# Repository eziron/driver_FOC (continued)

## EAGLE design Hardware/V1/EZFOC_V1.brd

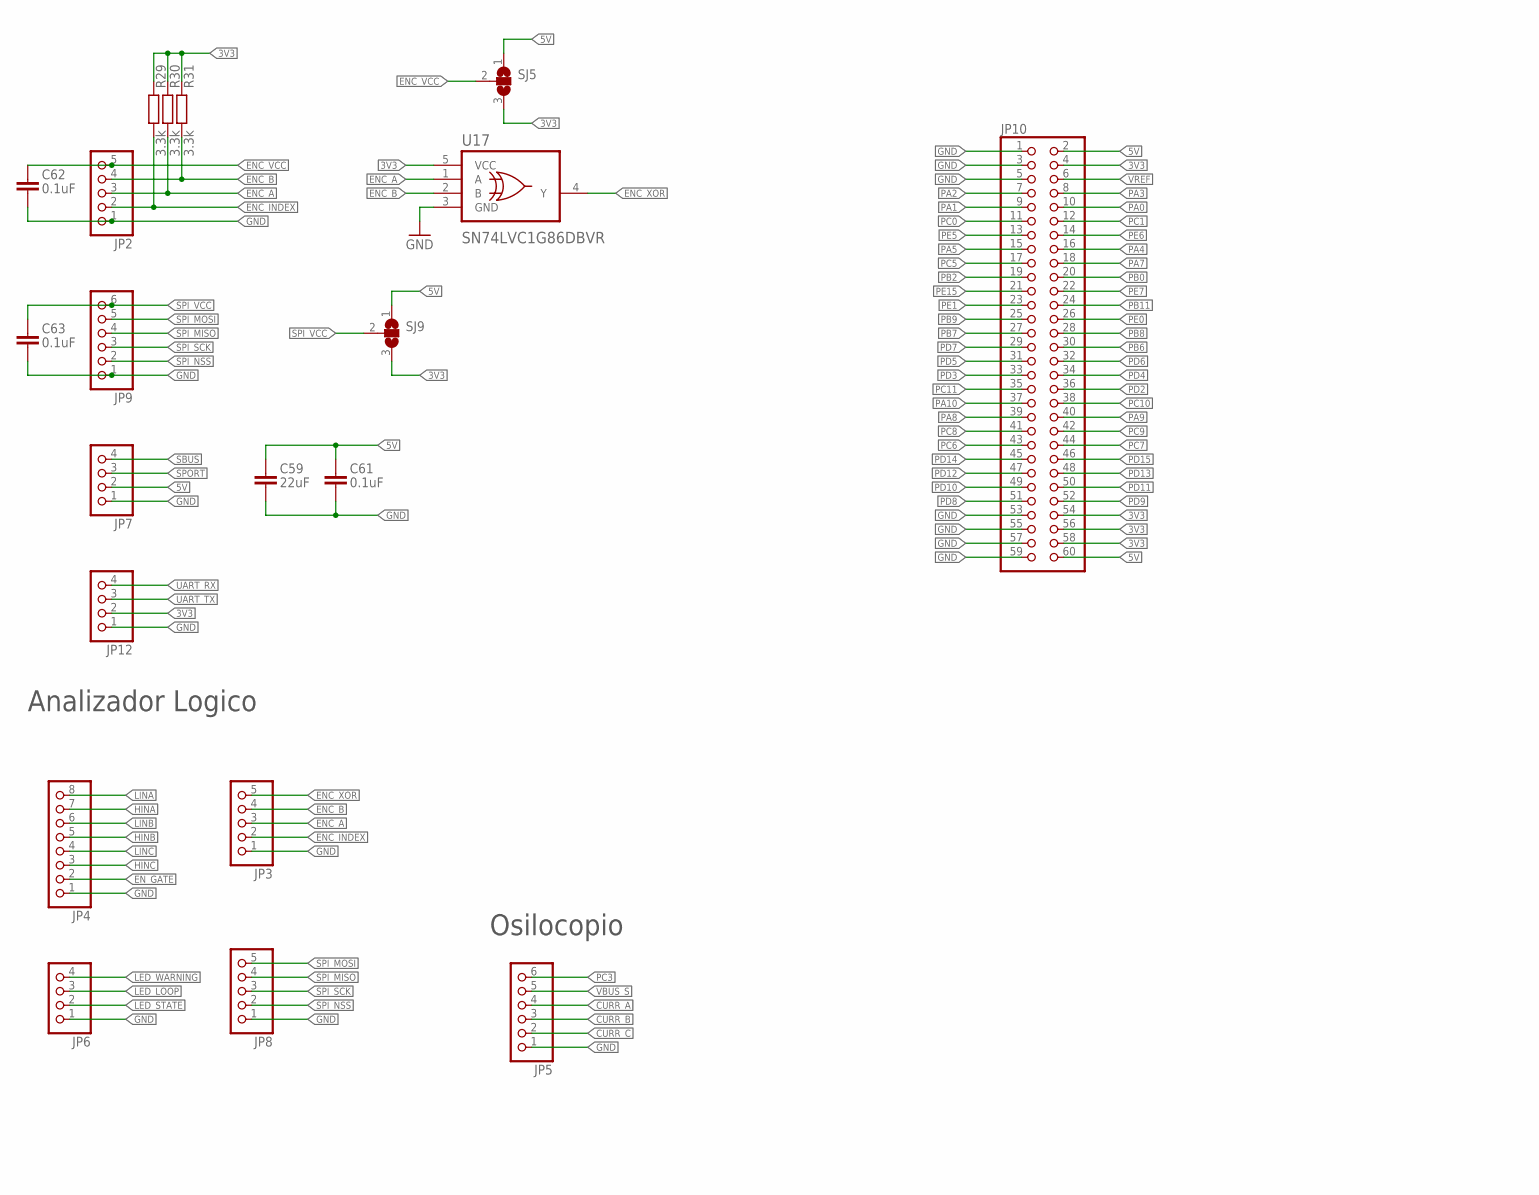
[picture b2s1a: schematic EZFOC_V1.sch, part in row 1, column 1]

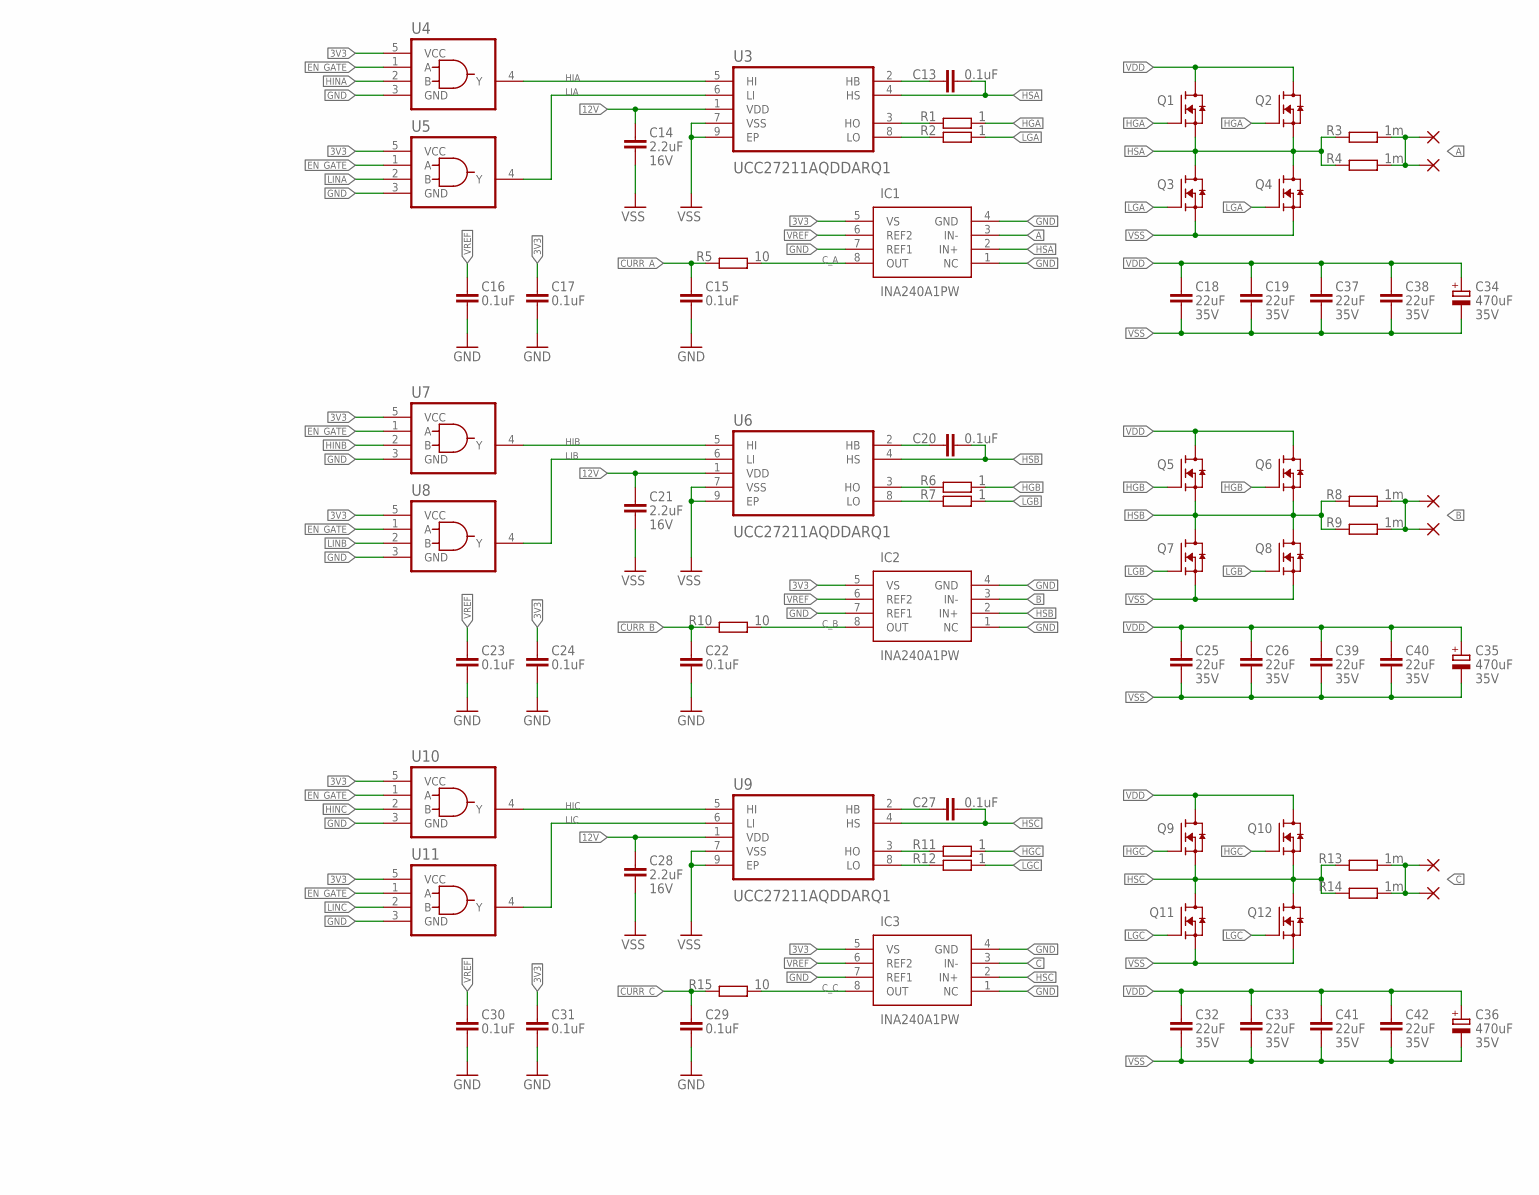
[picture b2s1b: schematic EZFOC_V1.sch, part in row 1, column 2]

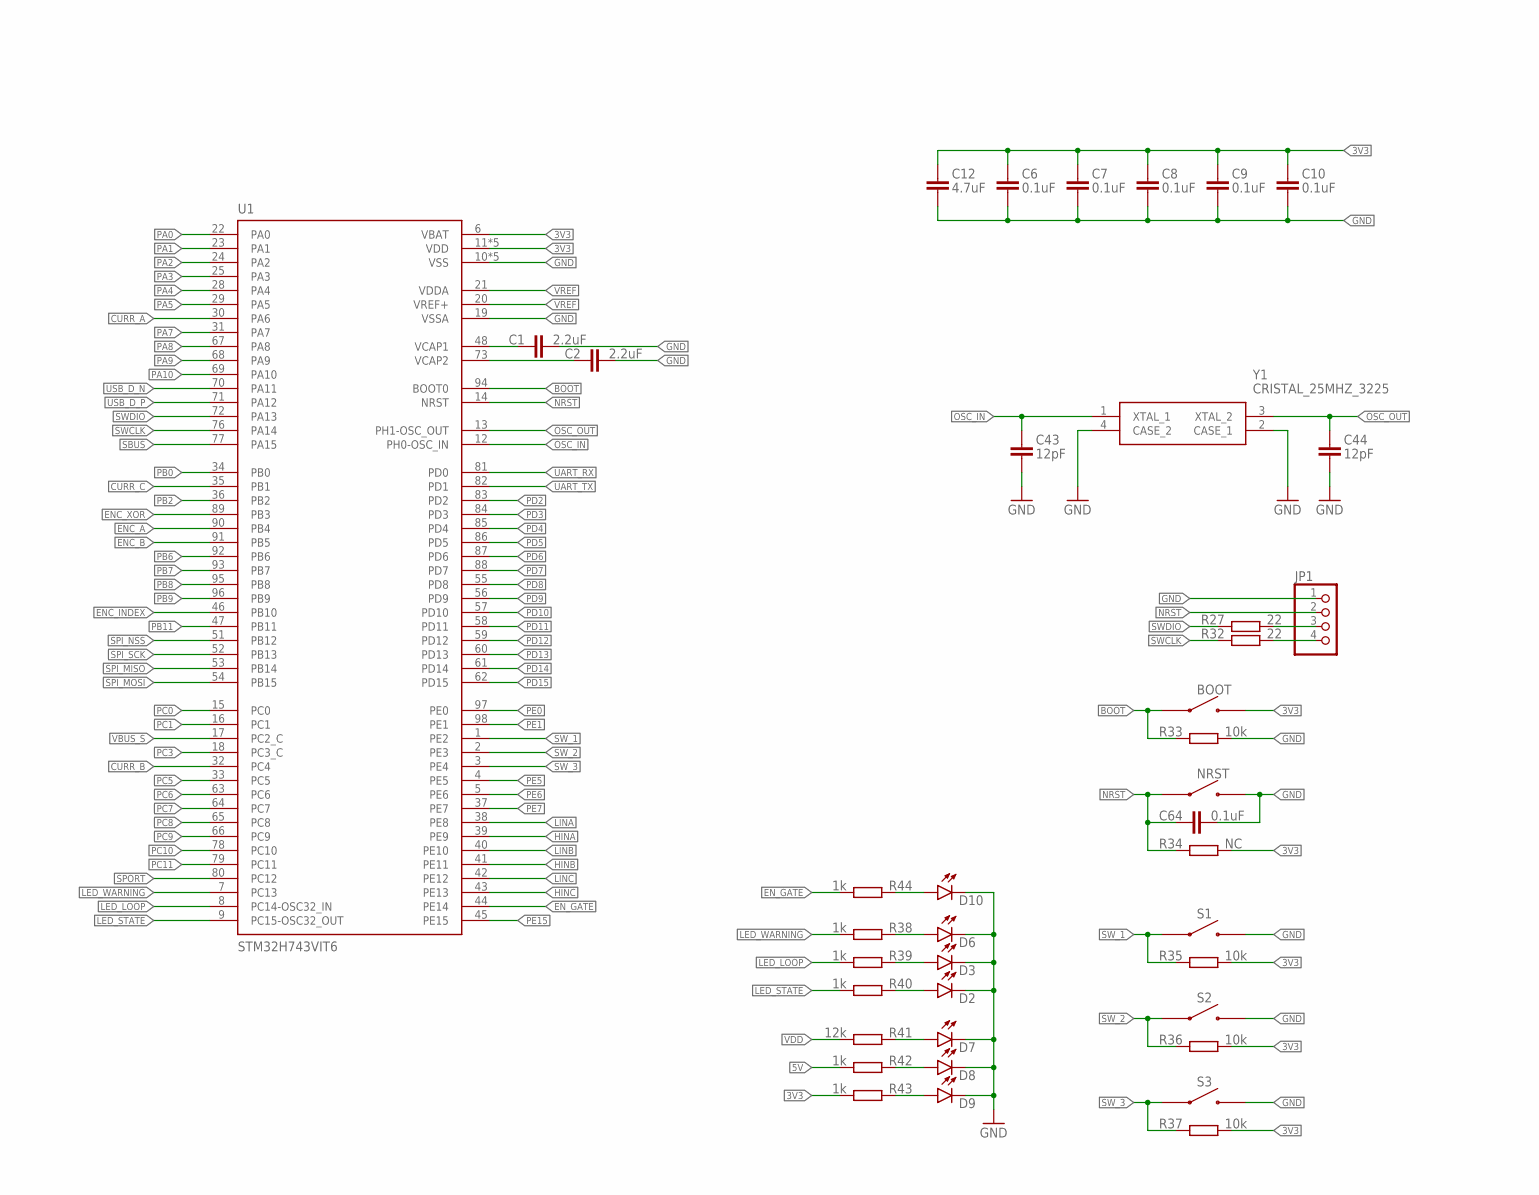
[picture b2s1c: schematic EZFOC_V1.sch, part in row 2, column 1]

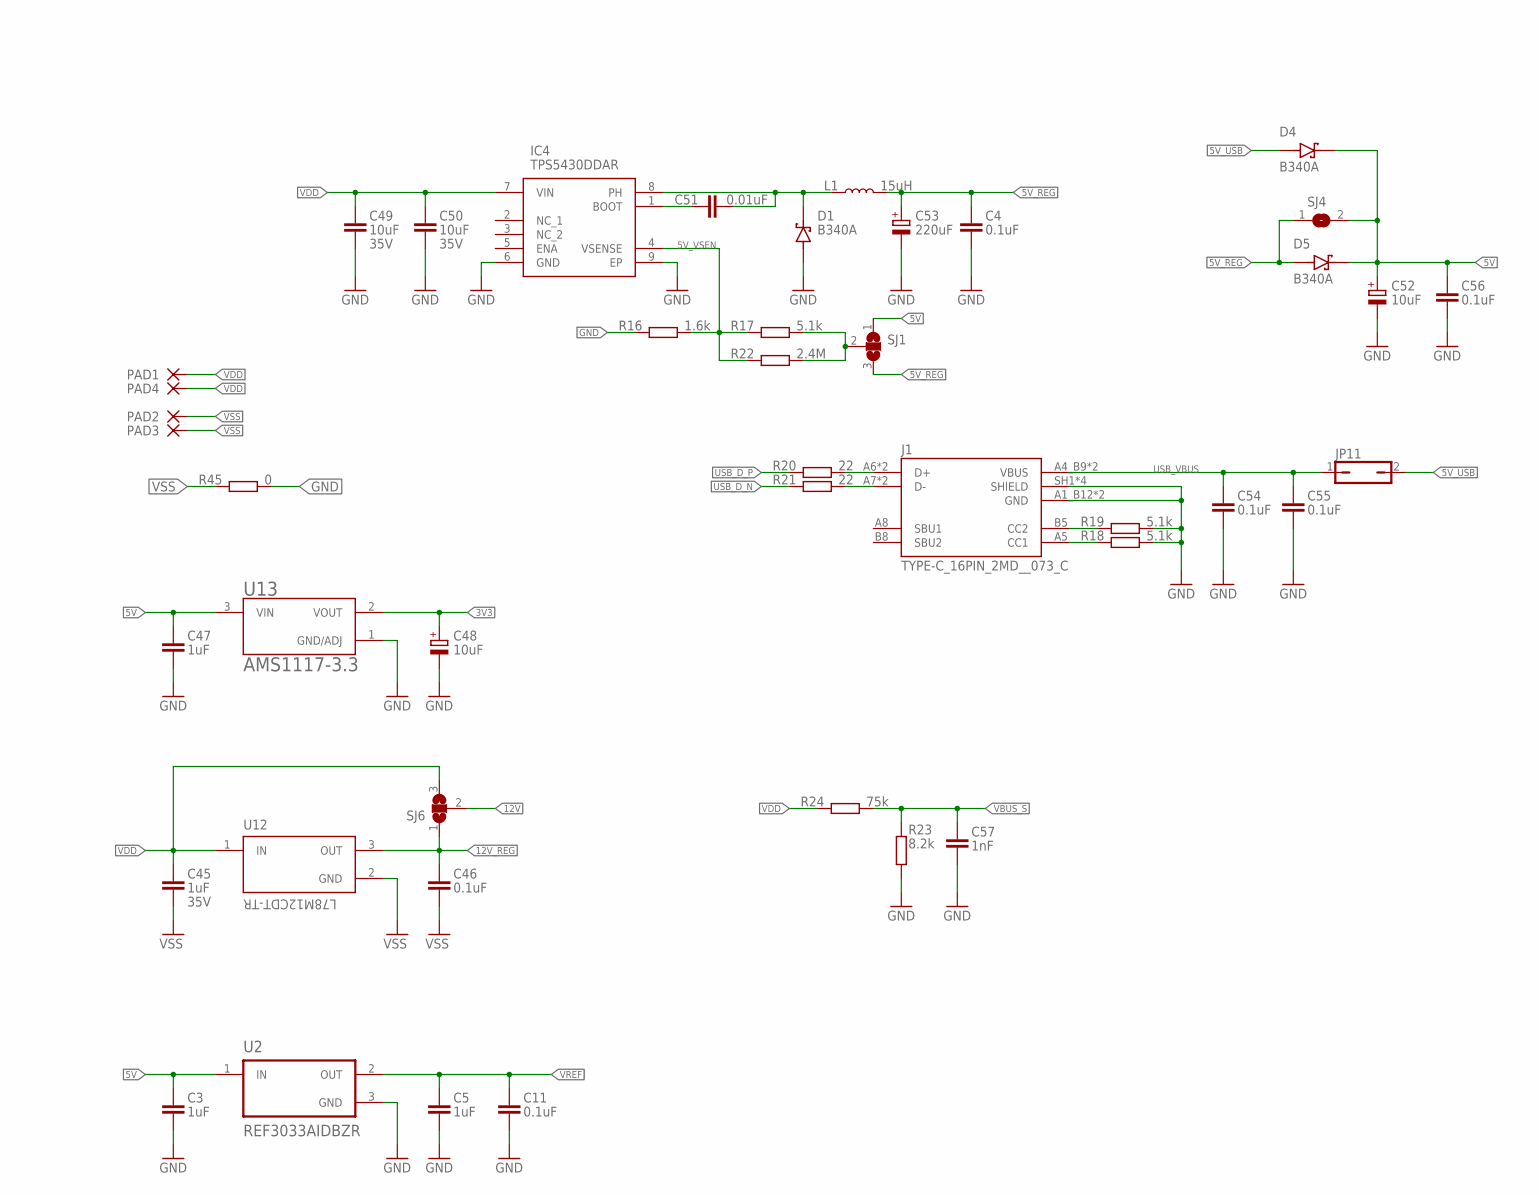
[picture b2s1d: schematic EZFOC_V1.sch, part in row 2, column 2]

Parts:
A, A1: PAD1.27X2.54; SMD1,27-2,54
B, B1: PAD1.27X2.54; SMD1,27-2,54
BOOT: TS-1088; SKRKAEE020
C, C65: PAD1.27X2.54; SMD1,27-2,54
C1, C2: 2.2uF; 0603
C3, C5, C45, C47: 1uF; 0603; VOLTAGE_RATING 35V
C4, C6, C7, C8, C9, C10, C11, C15, C16, C17, C22, C23, C24, C29, C30, C31, C46, C54, C55, C56, C61, C62, C63, C64: 0.1uF; 0402
C12: 4.7uF; 0603
C13, C20, C27: 0.1uF; 0603; VOLTAGE_RATING 35V
C14, C21, C28: 2.2uF; 0603; VOLTAGE_RATING 16V
C18, C19, C25, C26, C32, C33, C37, C38, C39, C40, C41, C42, C59: 22uF; 1206; VOLTAGE_RATING 35V
C34, C35, C36: 470uF; CAPAE1030X1050N; VOLTAGE_RATING 35V; JLCPCB C2980172
C43, C44: 12pF; 0402
C48, C52: 10uF; CAPMP3216X180N; JLCPCB C7171
C49, C50: 10uF; 0805; VOLTAGE_RATING 35V
C51: 0.01uF; 0603
C53: 220uF; CAPAE660X800N; JLCPCB C72494
C57: 1nF; 0402
D1, D4, D5: B340A; DIOM5226X240N; JLCPCB C8678
D2, D3: LED_BLUE; LEDC2012X110N_FLAT-B; JLCPCB C965817
D6: LED_BLUE; LEDC2012X110N_FLAT-B; JLCPCB C2296
D7, D8, D9: LED_BLUE; LEDC2012X110N_FLAT-B; JLCPCB C84256
D10: LED_BLUE; LEDC2012X110N_FLAT-B; JLCPCB C2297
IC1, IC2, IC3: INA240A1PW; SOP65P640X120-8N; JLCPCB C93965
IC4: TPS5430DDAR; SOIC127P600X170-9N
J1: TYPE-C_16PIN_2MD__073_C; GCT_USB4105-GF-A
JP1, JP6, JP7, JP12: PINHD-1X4; 1X04
JP2, JP3, JP8: PINHD-1X5; 1X05
JP4: PINHD-1X8; 1X08
JP5, JP9: PINHD-1X6; 1X06
JP10: PINHD-2X30; 2X30
JP11: JP1Q; JP1
L1: 15uH; SMD6.6X7.3MM
NRST: TS-1088; SKRKAEE020
PAD1, PAD2, PAD3, PAD4: PAD2.54X5.08; SMD2,54-5,08
Q1, Q2, Q3, Q4, Q5, Q6, Q7, Q8, Q9, Q10, Q11, Q12: BSC011N03LSI_FL; TDSON-8FL
R1, R2, R6, R7, R11, R12: 1; 0603
R3, R4, R8, R9, R13, R14: 1m; 2512; JLCPCB C7370895
R5, R10, R15: 10; 0402
R16: 1.6k; 0603
R17, R18, R19: 5.1k; 0603
R20, R21, R27, R32: 22; 0402
R22: 2.4M; 0603
R23: 8.2k; 0603
R24: 75k; 0603
R29, R30, R31: 3.3k; 0402
R33, R35, R36, R37: 10k; 0402
R34: NC; 0402
R38, R39, R40, R42, R43, R44: 1k; 0402
R41: 12k; 0402
R45: 0; 1206; JLCPCB C17888
S1, S2, S3: TS-1088; SKRKAEE020
SJ1, SJ5, SJ6, SJ9: SJ2W; SJ_2
SJ4: SJ
U1: STM32H743VIT6; LQFP100
U2: REF3033AIDBZR; SOT95P237X112-3N
U3, U6, U9: UCC27211AQDDARQ1; SOIC127P600X170-9N
U4, U5, U7, U8, U10, U11: SN74LVC1G08DBVR; SOT95P280X145-5N
U12: L78M12CDT-TR; VREG_L78M12CDT-TR
U13: AMS1117-3.3; SOT229P700X180-4N
U17: SN74LVC1G86DBVR; SOT95P280X145-5N
Y1: CRISTAL_25MHZ_3225; SMD3225-4P

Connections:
3V3: BOOT.2, C6.1, C7.1, C8.1, C9.1, C10.1, C12.1, C17.1, C24.1, C31.1, C48.1 (+), IC1.5 (VS), IC2.5 (VS), IC3.5 (VS), JP10.4, JP10.54, JP10.56, JP10.58, JP12.2, R29.1, R30.1, R31.1, R34.2, R35.2, R36.2, R37.2, R43.2, SJ5.3, SJ9.3, U1.6 (VBAT), U1.11 (VDD), U1.27 (VDD), U1.50 (VDD), U1.75 (VDD), U1.100 (VDD), U4.5 (VCC), U5.5 (VCC), U7.5 (VCC), U8.5 (VCC), U10.5 (VCC), U11.5 (VCC), U13.2 (VOUT), U17.5 (VCC)
5V: C3.1, C47.1, C52.1 (+), C56.1, C59.1, C61.1, D4.C, D5.C, JP7.2, JP10.2, JP10.60, R42.2, SJ1.1, SJ4.2, SJ5.1, SJ9.1, U2.1 (IN), U13.3 (VIN)
5V_REG: C4.1, C53.1 (+), D5.A, L1.2, SJ1.3, SJ4.1
5V_USB: D4.A, JP11.2
5V_VSEN: IC4.4 (VSENSE), R16.2, R17.1, R22.1
12V: C14.1, C21.1, C28.1, SJ6.2, U3.1 (VDD), U6.1 (VDD), U9.1 (VDD)
12V_REG: C46.1, SJ6.1, U12.3 (OUT)
A: A.1, A1.1, IC1.3 (IN-), R3.2, R4.2
B: B.1, B1.1, IC2.3 (IN-), R8.2, R9.2
BOOT: BOOT.1, R33.1, U1.94 (BOOT0)
C: C.1, C65.1, IC3.3 (IN-), R13.2, R14.2
CURR_A: C15.1, JP5.4, R5.1, U1.30 (PA6)
CURR_B: C22.1, JP5.3, R10.1, U1.32 (PC4)
CURR_C: C29.1, JP5.2, R15.1, U1.35 (PB1)
C_A: IC1.8 (OUT), R5.2
C_B: IC2.8 (OUT), R10.2
C_C: IC3.8 (OUT), R15.2
ENC_A: JP2.3, JP3.3, R30.2, U1.90 (PB4), U17.1 (A)
ENC_B: JP2.4, JP3.4, R31.2, U1.91 (PB5), U17.2 (B)
ENC_INDEX: JP2.2, JP3.2, R29.2, U1.46 (PB10)
ENC_VCC: C62.1, JP2.5, SJ5.2
ENC_XOR: JP3.5, U1.89 (PB3), U17.4 (Y)
EN_GATE: JP4.2, R44.2, U1.44 (PE14), U4.1 (A), U5.1 (A), U7.1 (A), U8.1 (A), U10.1 (A), U11.1 (A)
EN_GATE_R: D10.A, R44.1
GND: C1.2, C2.2, C3.2, C4.2, C5.2, C6.2, C7.2, C8.2, C9.2, C10.2, C11.2, C12.2, C15.2, C16.2, C17.2, C22.2, C23.2, C24.2, C29.2, C30.2, C31.2, C43.2, C44.2, C47.2, C48.2 (-), C49.2, C50.2, C52.2 (-), C53.2 (-), C54.2, C55.2, C56.2, C57.2, C59.2, C61.2, C62.2, C63.2, C64.2, D1.A, D2.C, D3.C, D6.C, D7.C, D8.C, D9.C, D10.C, IC1.1 (NC), IC1.4 (GND), IC1.7 (REF1), IC2.1 (NC), IC2.4 (GND), IC2.7 (REF1), IC3.1 (NC), IC3.4 (GND), IC3.7 (REF1), IC4.6 (GND), IC4.9 (EP), J1.A1_B12 (GND), J1.B1_A12 (GND), J1.SH1 (SHIELD), J1.SH2 (SHIELD), J1.SH3 (SHIELD), J1.SH4 (SHIELD), JP1.1, JP2.1, JP3.1, JP4.1, JP5.1, JP6.1, JP7.1, JP8.1, JP9.1, JP10.1, JP10.3, JP10.5, JP10.53, JP10.55, JP10.57, JP10.59, JP12.1, NRST.2, R16.1, R18.2, R19.2, R23.1, R33.2, R45.2, S1.2, S2.2, S3.2, U1.10 (VSS), U1.19 (VSSA), U1.26 (VSS), U1.49 (VSS), U1.74 (VSS), U1.99 (VSS), U2.3 (GND), U4.3 (GND), U5.3 (GND), U7.3 (GND), U8.3 (GND), U10.3 (GND), U11.3 (GND), U13.1 (GND/ADJ), U17.3 (GND), Y1.2 (CASE_1), Y1.4 (CASE_2)
HBA: C13.1, U3.2 (HB)
HBB: C20.1, U6.2 (HB)
HBC: C27.1, U9.2 (HB)
HGA: Q1.4 (G), Q2.4 (G), R1.2
HGB: Q5.4 (G), Q6.4 (G), R6.2
HGC: Q9.4 (G), Q10.4 (G), R11.2
HIA: U3.5 (HI), U4.4 (Y)
HIB: U6.5 (HI), U7.4 (Y)
HIC: U9.5 (HI), U10.4 (Y)
HINA: JP4.7, U1.39 (PE9), U4.2 (B)
HINB: JP4.5, U1.41 (PE11), U7.2 (B)
HINC: JP4.3, U1.43 (PE13), U10.2 (B)
HOA: R1.1, U3.3 (HO)
HOB: R6.1, U6.3 (HO)
HOC: R11.1, U9.3 (HO)
HSA: C13.2, IC1.2 (IN+), Q1.1 (S), Q1.2 (S), Q1.3 (S), Q1.10 (S), Q2.1 (S), Q2.2 (S), Q2.3 (S), Q2.10 (S), Q3.5 (D), Q3.6 (D), Q3.7 (D), Q3.8 (D), Q3.9 (D), Q4.5 (D), Q4.6 (D), Q4.7 (D), Q4.8 (D), Q4.9 (D), R3.1, R4.1, U3.4 (HS)
HSB: C20.2, IC2.2 (IN+), Q5.1 (S), Q5.2 (S), Q5.3 (S), Q5.10 (S), Q6.1 (S), Q6.2 (S), Q6.3 (S), Q6.10 (S), Q7.5 (D), Q7.6 (D), Q7.7 (D), Q7.8 (D), Q7.9 (D), Q8.5 (D), Q8.6 (D), Q8.7 (D), Q8.8 (D), Q8.9 (D), R8.1, R9.1, U6.4 (HS)
HSC: C27.2, IC3.2 (IN+), Q9.1 (S), Q9.2 (S), Q9.3 (S), Q9.10 (S), Q10.1 (S), Q10.2 (S), Q10.3 (S), Q10.10 (S), Q11.5 (D), Q11.6 (D), Q11.7 (D), Q11.8 (D), Q11.9 (D), Q12.5 (D), Q12.6 (D), Q12.7 (D), Q12.8 (D), Q12.9 (D), R13.1, R14.1, U9.4 (HS)
LED1R: D6.A, R38.1
LED2R: D3.A, R39.1
LED3R: D2.A, R40.1
LED4R: D7.A, R41.1
LED5R: D8.A, R42.1
LED6R: D9.A, R43.1
LED_LOOP: JP6.3, R39.2, U1.8 (PC14-OSC32_IN)
LED_STATE: JP6.2, R40.2, U1.9 (PC15-OSC32_OUT)
LED_WARNING: JP6.4, R38.2, U1.7 (PC13)
LGA: Q3.4 (G), Q4.4 (G), R2.2
LGB: Q7.4 (G), Q8.4 (G), R7.2
LGC: Q11.4 (G), Q12.4 (G), R12.2
LIA: U3.6 (LI), U5.4 (Y)
LIB: U6.6 (LI), U8.4 (Y)
LIC: U9.6 (LI), U11.4 (Y)
LINA: JP4.8, U1.38 (PE8), U5.2 (B)
LINB: JP4.6, U1.40 (PE10), U8.2 (B)
LINC: JP4.4, U1.42 (PE12), U11.2 (B)
LOA: R2.1, U3.8 (LO)
LOB: R7.1, U6.8 (LO)
LOC: R12.1, U9.8 (LO)
NRST: C64.1, JP1.2, NRST.1, R34.1, U1.14 (NRST)
OSC_IN: C43.1, U1.12 (PH0-OSC_IN), Y1.1 (XTAL_1)
OSC_OUT: C44.1, U1.13 (PH1-OSC_OUT), Y1.3 (XTAL_2)
PA0: JP10.10, U1.22 (PA0)
PA1: JP10.9, U1.23 (PA1)
PA2: JP10.7, U1.24 (PA2)
PA3: JP10.8, U1.25 (PA3)
PA4: JP10.16, U1.28 (PA4)
PA5: JP10.15, U1.29 (PA5)
PA7: JP10.18, U1.31 (PA7)
PA8: JP10.39, U1.67 (PA8)
PA9: JP10.40, U1.68 (PA9)
PA10: JP10.37, U1.69 (PA10)
PB0: JP10.20, U1.34 (PB0)
PB2: JP10.19, U1.36 (PB2)
PB6: JP10.30, U1.92 (PB6)
PB7: JP10.27, U1.93 (PB7)
PB8: JP10.28, U1.95 (PB8)
PB9: JP10.25, U1.96 (PB9)
PB11: JP10.24, U1.47 (PB11)
PC0: JP10.11, U1.15 (PC0)
PC1: JP10.12, U1.16 (PC1)
PC3: JP5.6, U1.18 (PC3_C)
PC5: JP10.17, U1.33 (PC5)
PC6: JP10.43, U1.63 (PC6)
PC7: JP10.44, U1.64 (PC7)
PC8: JP10.41, U1.65 (PC8)
PC9: JP10.42, U1.66 (PC9)
PC10: JP10.38, U1.78 (PC10)
PC11: JP10.35, U1.79 (PC11)
PD2: JP10.36, U1.83 (PD2)
PD3: JP10.33, U1.84 (PD3)
PD4: JP10.34, U1.85 (PD4)
PD5: JP10.31, U1.86 (PD5)
PD6: JP10.32, U1.87 (PD6)
PD7: JP10.29, U1.88 (PD7)
PD8: JP10.51, U1.55 (PD8)
PD9: JP10.52, U1.56 (PD9)
PD10: JP10.49, U1.57 (PD10)
PD11: JP10.50, U1.58 (PD11)
PD12: JP10.47, U1.59 (PD12)
PD13: JP10.48, U1.60 (PD13)
PD14: JP10.45, U1.61 (PD14)
PD15: JP10.46, U1.62 (PD15)
PE0: JP10.26, U1.97 (PE0)
PE1: JP10.23, U1.98 (PE1)
PE5: JP10.13, U1.4 (PE5)
PE6: JP10.14, U1.5 (PE6)
PE7: JP10.22, U1.37 (PE7)
PE15: JP10.21, U1.45 (PE15)
REG_BOOT: C51.1, IC4.1 (BOOT)
REG_PH: C51.2, D1.C, IC4.8 (PH), L1.1
SBUS: JP7.4, U1.77 (PA15)
SJ1_SEL: R17.2, R22.2, SJ1.2
SPI_MISO: JP8.4, JP9.4, U1.53 (PB14)
SPI_MOSI: JP8.5, JP9.5, U1.54 (PB15)
SPI_NSS: JP8.2, JP9.2, U1.51 (PB12)
SPI_SCK: JP8.3, JP9.3, U1.52 (PB13)
SPI_VCC: C63.1, JP9.6, SJ9.2
SPORT: JP7.3, U1.80 (PC12)
SWCLK: R32.1, U1.76 (PA14)
SWCLK_R: JP1.4, R32.2
SWDIO: R27.1, U1.72 (PA13)
SWDIO_R: JP1.3, R27.2
SW_1: R35.1, S1.1, U1.1 (PE2)
SW_2: R36.1, S2.1, U1.2 (PE3)
SW_3: R37.1, S3.1, U1.3 (PE4)
UART_RX: JP12.4, U1.81 (PD0)
UART_TX: JP12.3, U1.82 (PD1)
USB_CC1: J1.B5 (CC2), R19.1
USB_CC2: J1.A5 (CC1), R18.1
USB_DN_R: J1.A7 (D-), J1.B7 (D-), R21.2
USB_DP_R: J1.A6 (D+), J1.B6 (D+), R20.2
USB_D_N: R21.1, U1.70 (PA11)
USB_D_P: R20.1, U1.71 (PA12)
USB_VBUS: C54.1, C55.1, J1.A4_B9 (VBUS), J1.B4_A9 (VBUS), JP11.1
VBUS_S: C57.1, JP5.5, R23.2, R24.2, U1.17 (PC2_C)
VCAP1: C1.1, U1.48 (VCAP1)
VCAP2: C2.1, U1.73 (VCAP2)
VDD: C18.1, C19.1, C25.1, C26.1, C32.1, C33.1, C34.1 (+), C35.1 (+), C36.1 (+), C37.1, C38.1, C39.1, C40.1, C41.1, C42.1, C45.1, C49.1, C50.1, IC4.7 (VIN), PAD1.1, PAD4.1, Q1.5 (D), Q1.6 (D), Q1.7 (D), Q1.8 (D), Q1.9 (D), Q2.5 (D), Q2.6 (D), Q2.7 (D), Q2.8 (D), Q2.9 (D), Q5.5 (D), Q5.6 (D), Q5.7 (D), Q5.8 (D), Q5.9 (D), Q6.5 (D), Q6.6 (D), Q6.7 (D), Q6.8 (D), Q6.9 (D), Q9.5 (D), Q9.6 (D), Q9.7 (D), Q9.8 (D), Q9.9 (D), Q10.5 (D), Q10.6 (D), Q10.7 (D), Q10.8 (D), Q10.9 (D), R24.1, R41.2, SJ6.3, U12.1 (IN)
VREF: C5.1, C11.1, C16.1, C23.1, C30.1, IC1.6 (REF2), IC2.6 (REF2), IC3.6 (REF2), JP10.6, U1.20 (VREF+), U1.21 (VDDA), U2.2 (OUT)
VSS: C14.2, C18.2, C19.2, C21.2, C25.2, C26.2, C28.2, C32.2, C33.2, C34.2 (-), C35.2 (-), C36.2 (-), C37.2, C38.2, C39.2, C40.2, C41.2, C42.2, C45.2, C46.2, PAD2.1, PAD3.1, Q3.1 (S), Q3.2 (S), Q3.3 (S), Q3.10 (S), Q4.1 (S), Q4.2 (S), Q4.3 (S), Q4.10 (S), Q7.1 (S), Q7.2 (S), Q7.3 (S), Q7.10 (S), Q8.1 (S), Q8.2 (S), Q8.3 (S), Q8.10 (S), Q11.1 (S), Q11.2 (S), Q11.3 (S), Q11.10 (S), Q12.1 (S), Q12.2 (S), Q12.3 (S), Q12.10 (S), R45.1, U3.7 (VSS), U3.9 (EP), U6.7 (VSS), U6.9 (EP), U9.7 (VSS), U9.9 (EP), U12.2 (GND)

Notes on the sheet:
Analizador Logico
Osilocopio

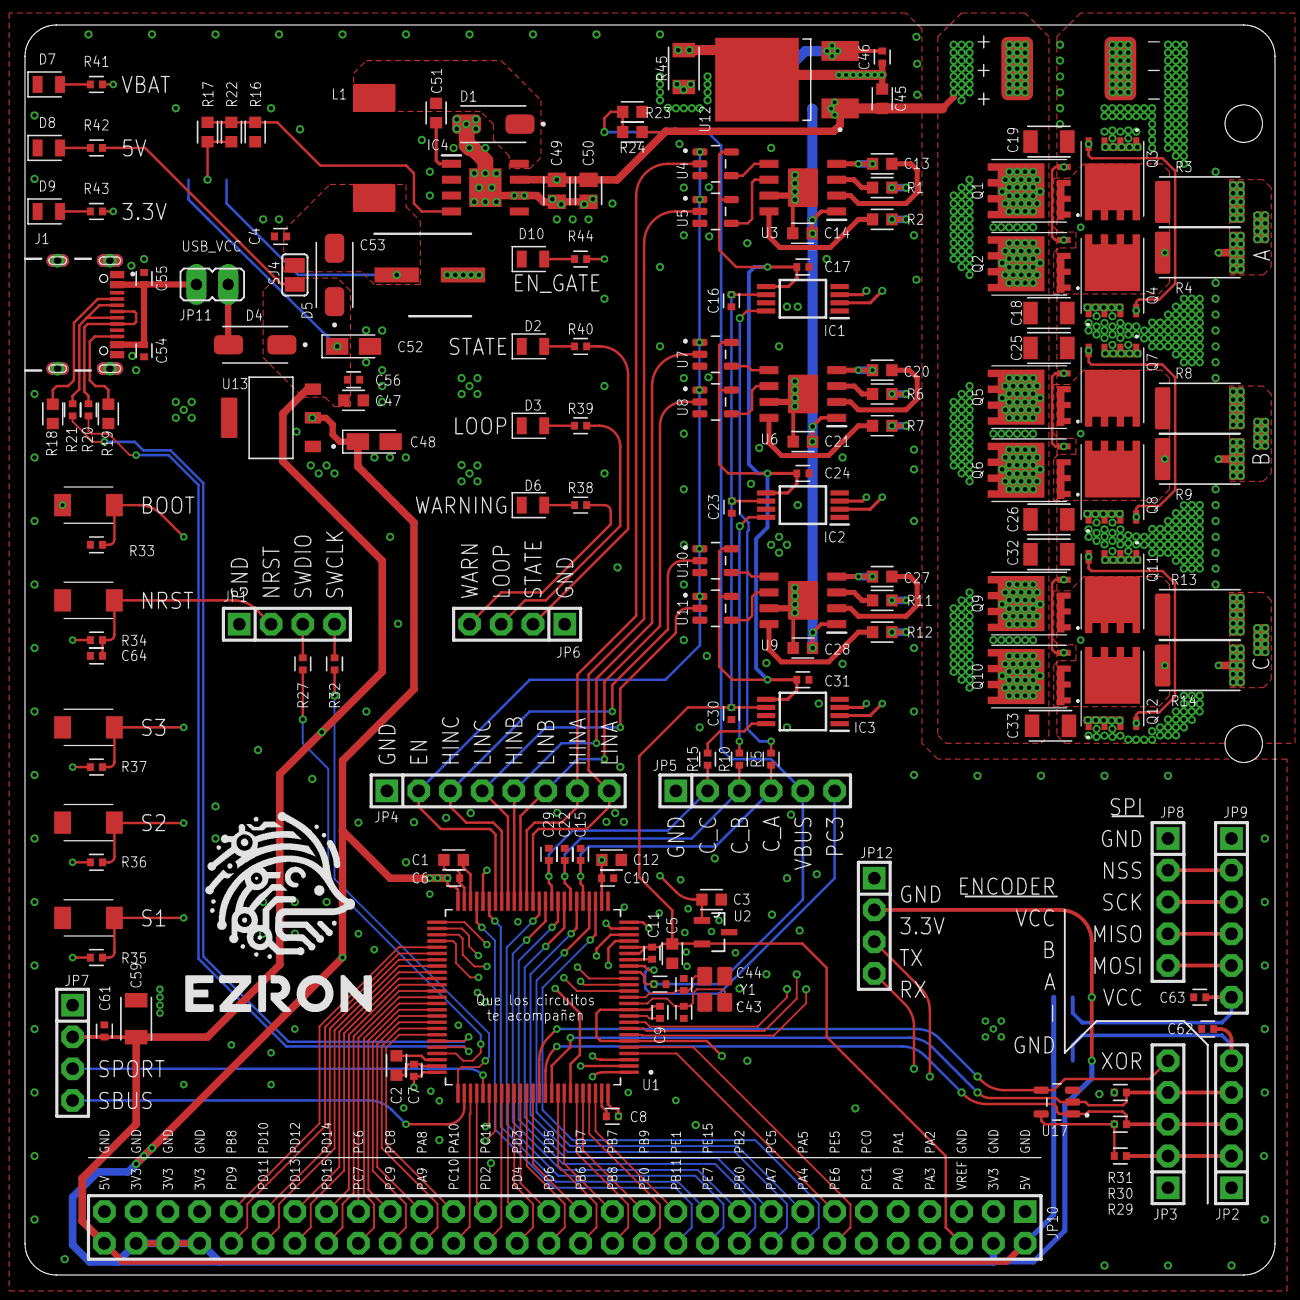
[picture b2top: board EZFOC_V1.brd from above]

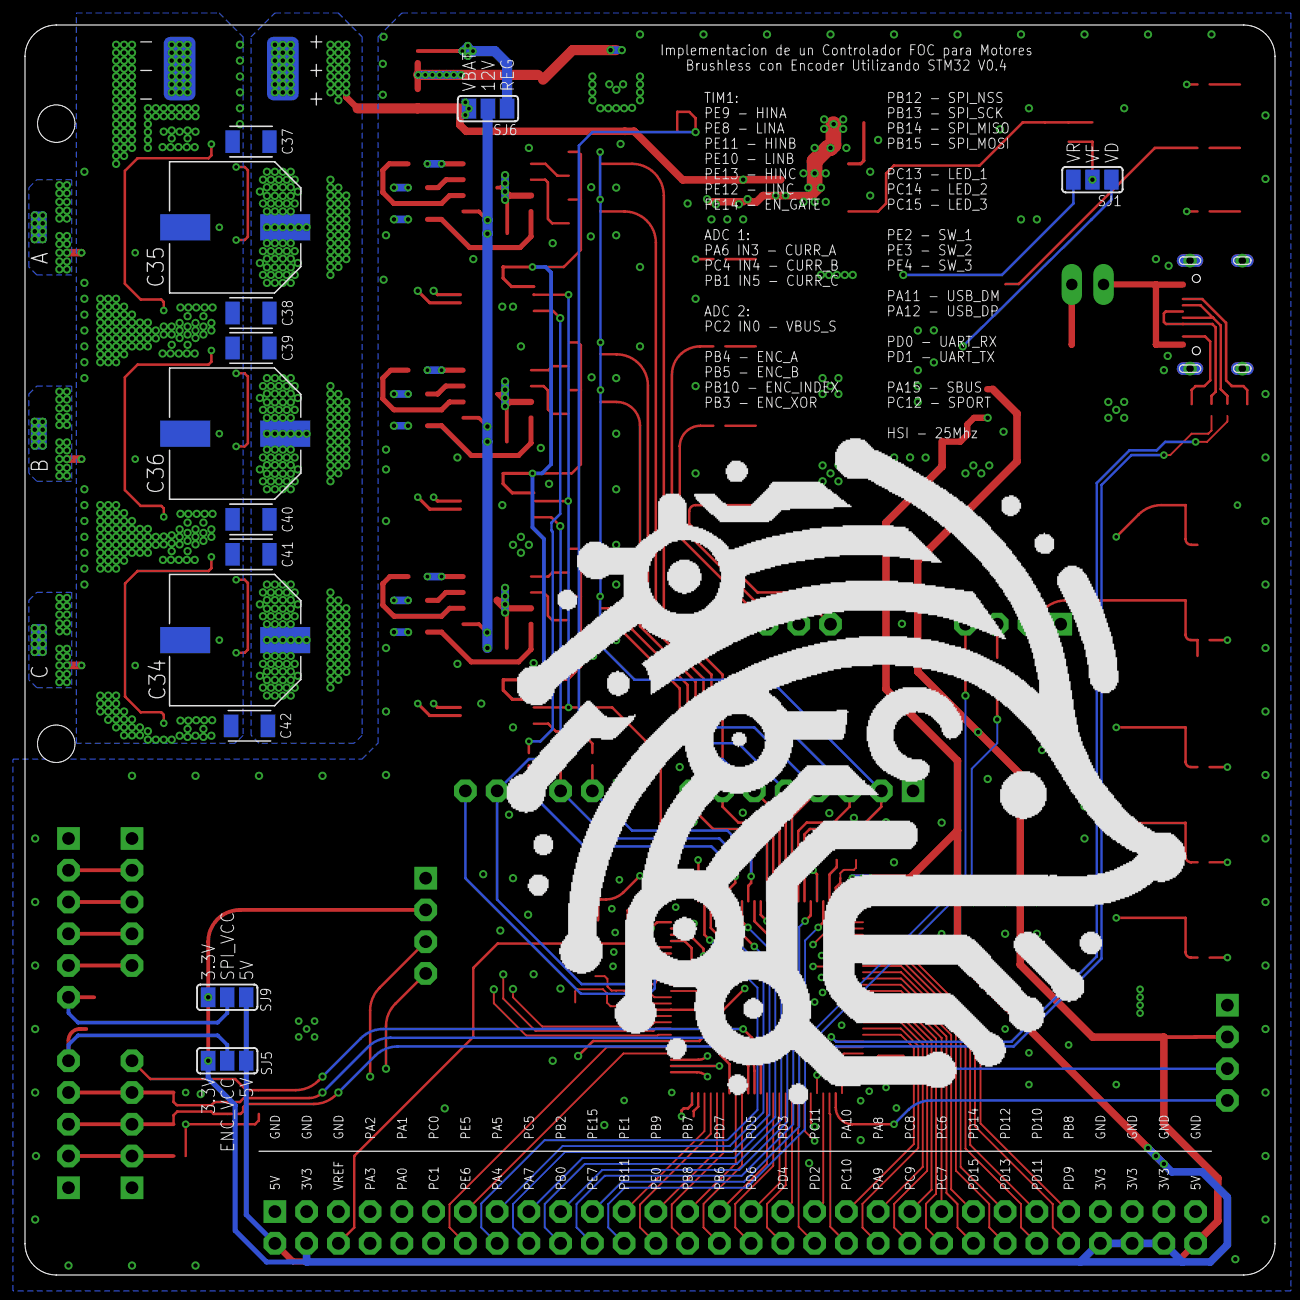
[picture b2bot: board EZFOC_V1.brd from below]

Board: 4 copper layers, 100.0 x 100.0 mm, 179 parts (18 on the bottom side), 146 nets.

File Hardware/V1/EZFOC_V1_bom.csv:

Comment,Designator,Footprint,LCSC Part #
,JP1,1X04,
,JP6,1X04,
,JP7,1X04,
,JP12,1X04,
,JP2,1X05,
,JP3,1X05,
,JP8,1X05,
,JP5,1X06,
,JP9,1X06,
,JP4,1X08,
,JP10,2X30,
,JP11,JP1,
,SJ4,SJ,
,SJ1,SJ_2,
,SJ5,SJ_2,
,SJ6,SJ_2,
,SJ9,SJ_2,
0,R45,1206,C17888
0.1uF,C4 C6 C7 C8 C9 C10 C11 C15 C16 C17 C22 C23 C24 C29 C30 C31 C46 C54 C55 C56 C61 C62 C63 C64,0402,
0.1uF 35V,C13 C20 C27,0603,
0.01uF,C51,0603,
1,R1 R2 R6 R7 R11 R12,0603,
1.6k,R16,0603,
1k,R38 R39 R40 R42 R43 R44,0402,
1m,R3 R4 R8 R9 R13 R14,2512,C7370895
1nF,C57,0402,
1uF 35V,C3 C5 C45 C47,0603,
2.2uF,C1 C2,0603,
2.2uF 16V,C14 C21 C28,0603,
2.4M,R22,0603,
3.3k,R29 R30 R31,0402,
4.7uF,C12,0603,
5.1k,R17 R18 R19,0603,
8.2k,R23,0603,
10,R5 R10 R15,0402,
10k,R33 R35 R36 R37,0402,
10uF 35V,C49 C50,0805,
10uF,C48 C52,CAPMP3216X180N,C7171
12k,R41,0402,
12pF,C43 C44,0402,
15uH,L1,SMD6.6X7.3MM,C2847544
22,R20 R21 R27 R32,0402,
22uF 35V,C18 C19 C25 C26 C32 C33 C37 C38 C39 C40 C41 C42 C59,1206,
75k,R24,0603,
220uF,C53,CAPAE660X800N, C72494
470uF 35V,C34 C35 C36,CAPAE1030X1050N,C2980172
AMS1117-3.3,U13,SOT229P700X180-4N,C6186
B340A,D1 D4 D5,DIOM5226X240N,C8678
BSC011N03LSI_FL,Q1 Q2 Q3 Q4 Q5 Q6 Q7 Q8 Q9 Q10 Q11 Q12,TDSON-8FL,C534283
CRISTAL_25MHZ_3225,Y1,SMD3225-4P,C9006
INA240A1PW,IC1 IC2 IC3,SOP65P640X120-8N,C93965
L78M12CDT-TR,U12,VREG_L78M12CDT-TR,C16424
LED_BLUE,D2 D3 D6 D7 D8 D9 D10,LEDC2012X110N_FLAT-B,C2297
NC,R34,0402,
PAD1.27X2.54,A A1 B B1 C C65,SMD1 27-2 54,
PAD2.54X5.08,PAD1 PAD2 PAD3 PAD4,SMD2 54-5 08,
REF3033AIDBZR,U2,SOT95P237X112-3N,C36658
SN74LVC1G08DBVR,U4 U5 U7 U8 U10 U11,SOT95P280X145-5N,C7666
SN74LVC1G86DBVR,U17,SOT95P280X145-5N,C402161
STM32H743VIT6,U1,LQFP100,C114409
TPS5430DDAR,IC4,SOIC127P600X170-9N,C9864
TS-1088,BOOT NRST S1 S2 S3,SKRKAEE020,C720477
TYPE-C_16PIN_2MD__073_C,J1,GCT_USB4105-GF-A,
UCC27211AQDDARQ1,U3 U6 U9,SOIC127P600X170-9N,C485921

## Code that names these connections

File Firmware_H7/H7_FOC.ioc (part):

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Mcu.Name=STM32H743VITx
Mcu.Package=LQFP100
Mcu.UserName=STM32H743VITx
PA11.GPIOParameters=GPIO_Label
PA11.GPIO_Label=USB_DM
PA11.Mode=Device_Only
PA11.Signal=USB_OTG_FS_DM
PA12.GPIOParameters=GPIO_Label
PA12.GPIO_Label=USB_DP
PA12.Mode=Device_Only
PA12.Signal=USB_OTG_FS_DP
PA13\ (JTMS/SWDIO).GPIOParameters=GPIO_Label
PA13\ (JTMS/SWDIO).GPIO_Label=SWDIO
PA13\ (JTMS/SWDIO).Mode=Serial_Wire
PA13\ (JTMS/SWDIO).Signal=DEBUG_JTMS-SWDIO
PA14\ (JTCK/SWCLK).GPIOParameters=GPIO_Label
PA14\ (JTCK/SWCLK).GPIO_Label=SWCLK
PA14\ (JTCK/SWCLK).Mode=Serial_Wire
PA14\ (JTCK/SWCLK).Signal=DEBUG_JTCK-SWCLK
PA15\ (JTDI).GPIOParameters=GPIO_Label
PA15\ (JTDI).GPIO_Label=SBUS
PA15\ (JTDI).Mode=Half_duplex(single_wire_mode)
PA15\ (JTDI).Signal=UART7_TX
PA6.GPIOParameters=GPIO_Label
PA6.GPIO_Label=CURR_A
PA6.Signal=ADCx_INP3
PB0.GPIOParameters=GPIO_Label
PB0.GPIO_Label=POT_A
PB0.Signal=ADCx_INP9
PB1.GPIOParameters=GPIO_Label
PB1.GPIO_Label=CURR_C
PB1.Signal=ADCx_INP5
PB10.GPIOParameters=GPIO_Label
PB10.GPIO_Label=ENC_INDEX
PB10.Signal=S_TIM2_CH3
PB12.GPIOParameters=GPIO_Label
PB12.GPIO_Label=SPI_NSS
PB12.Mode=NSS_Signal_Hard_Output
PB12.Signal=SPI2_NSS
PB13.GPIOParameters=GPIO_Label
PB13.GPIO_Label=SPI_SCK
PB13.Mode=Full_Duplex_Master
PB13.Signal=SPI2_SCK
PB14.GPIOParameters=GPIO_Label
PB14.GPIO_Label=SPI_MISO
PB14.Mode=Full_Duplex_Master
PB14.Signal=SPI2_MISO
PB15.GPIOParameters=GPIO_Label
PB15.GPIO_Label=SPI_MOSI
PB15.Mode=Full_Duplex_Master
PB15.Signal=SPI2_MOSI
PB3\ (JTDO/TRACESWO).GPIOParameters=GPIO_Label
PB3\ (JTDO/TRACESWO).GPIO_Label=ENC_XOR
PB3\ (JTDO/TRACESWO).Signal=S_TIM2_CH2
PB4\ (NJTRST).GPIOParameters=GPIO_Label
PB4\ (NJTRST).GPIO_Label=ENC_A
PB4\ (NJTRST).Signal=S_TIM3_CH1
PB5.GPIOParameters=GPIO_Label
PB5.GPIO_Label=ENC_B
PB5.Signal=S_TIM3_CH2
PC0.GPIOParameters=GPIO_Label
PC0.GPIO_Label=POT_B
PC0.Signal=ADCx_INP10
PC1.GPIOParameters=GPIO_Label
PC1.GPIO_Label=POR_C
PC1.Signal=ADCx_INP11
PC12.GPIOParameters=GPIO_Label
PC12.GPIO_Label=SPORT
PC12.Mode=Half_duplex(single_wire_mode)
PC12.Signal=UART5_TX
PC13.GPIOParameters=GPIO_Label
PC13.GPIO_Label=LED_WARNING
PC13.Signal=GPIO_Output
PC14-OSC32_IN\ (OSC32_IN).GPIOParameters=GPIO_Label
PC14-OSC32_IN\ (OSC32_IN).GPIO_Label=LED_LOOP
PC14-OSC32_IN\ (OSC32_IN).Signal=GPIO_Output
PC15-OSC32_OUT\ (OSC32_OUT).GPIOParameters=GPIO_Label
PC15-OSC32_OUT\ (OSC32_OUT).GPIO_Label=LED_STATE
PC15-OSC32_OUT\ (OSC32_OUT).Signal=GPIO_Output
PC2_C.GPIOParameters=GPIO_Label
PC2_C.GPIO_Label=VBUS_S
PC2_C.Mode=IN0-Single-Ended
PC2_C.Signal=ADC3_INP0
PC4.GPIOParameters=GPIO_Label
PC4.GPIO_Label=CURR_B
PC4.Signal=ADCx_INP4
PD0.GPIOParameters=GPIO_Label
PD0.GPIO_Label=UART_RX
PD0.Mode=Asynchronous
PD0.Signal=UART4_RX
PD1.GPIOParameters=GPIO_Label
PD1.GPIO_Label=UART_TX
PD1.Mode=Asynchronous
PD1.Signal=UART4_TX
PE10.GPIOParameters=GPIO_Speed,GPIO_PuPd,GPIO_Label
PE10.GPIO_Label=LINB
PE10.GPIO_PuPd=GPIO_PULLDOWN
PE10.GPIO_Speed=GPIO_SPEED_FREQ_VERY_HIGH
PE10.Mode=PWM Generation2 CH2 CH2N
PE10.Signal=TIM1_CH2N
PE11.GPIOParameters=GPIO_Speed,GPIO_PuPd,GPIO_Label
PE11.GPIO_Label=HINB
PE11.GPIO_PuPd=GPIO_PULLDOWN
PE11.GPIO_Speed=GPIO_SPEED_FREQ_VERY_HIGH
PE11.Signal=S_TIM1_CH2
PE12.GPIOParameters=GPIO_Speed,GPIO_PuPd,GPIO_Label
PE12.GPIO_Label=LINC
PE12.GPIO_PuPd=GPIO_PULLDOWN
PE12.GPIO_Speed=GPIO_SPEED_FREQ_VERY_HIGH
PE12.Mode=PWM Generation3 CH3 CH3N
PE12.Signal=TIM1_CH3N
PE13.GPIOParameters=GPIO_Speed,GPIO_PuPd,GPIO_Label
PE13.GPIO_Label=HINC
PE13.GPIO_PuPd=GPIO_PULLDOWN
PE13.GPIO_Speed=GPIO_SPEED_FREQ_VERY_HIGH
PE13.Signal=S_TIM1_CH3
PE14.GPIOParameters=GPIO_Speed,GPIO_PuPd,GPIO_Label
PE14.GPIO_Label=EN_GATE
PE14.GPIO_PuPd=GPIO_PULLDOWN
PE14.GPIO_Speed=GPIO_SPEED_FREQ_VERY_HIGH
PE14.Signal=GPIO_Output
PE2.GPIOParameters=GPIO_Label
PE2.GPIO_Label=SW_1
PE2.Signal=GPIO_Input
PE3.GPIOParameters=GPIO_Label
PE3.GPIO_Label=SW_2
PE3.Signal=GPIO_Input
PE4.GPIOParameters=GPIO_Label
PE4.GPIO_Label=SW_3
PE4.Signal=GPIO_Input
PE5.Signal=S_TIM15_CH1
PE6.Signal=S_TIM15_CH2
PE8.GPIOParameters=GPIO_Speed,GPIO_PuPd,GPIO_Label
PE8.GPIO_Label=LINA
PE8.GPIO_PuPd=GPIO_PULLDOWN
PE8.GPIO_Speed=GPIO_SPEED_FREQ_VERY_HIGH
PE8.Mode=PWM Generation1 CH1 CH1N
PE8.Signal=TIM1_CH1N
PE9.GPIOParameters=GPIO_Speed,GPIO_PuPd,GPIO_Label
PE9.GPIO_Label=HINA
PE9.GPIO_PuPd=GPIO_PULLDOWN
PE9.GPIO_Speed=GPIO_SPEED_FREQ_VERY_HIGH
PE9.Signal=S_TIM1_CH1
PH0-OSC_IN\ (PH0).GPIOParameters=GPIO_Label
PH0-OSC_IN\ (PH0).GPIO_Label=OSC_IN
PH0-OSC_IN\ (PH0).Mode=HSE-External-Oscillator
PH0-OSC_IN\ (PH0).Signal=RCC_OSC_IN
PH1-OSC_OUT\ (PH1).GPIOParameters=GPIO_Label
PH1-OSC_OUT\ (PH1).GPIO_Label=OSC_OUT
PH1-OSC_OUT\ (PH1).Mode=HSE-External-Oscillator
PH1-OSC_OUT\ (PH1).Signal=RCC_OSC_OUT
RCC.SYSCLKFreq_VALUE=480000000
RCC.SYSCLKSource=RCC_SYSCLKSOURCE_PLLCLK
board=custom

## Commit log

2024-06-23 primer update
2024-06-23 add V0 harware
2024-06-23 debug code
2024-06-27 update 2706
2024-07-21 control trapezoidal
2024-07-28 DTC update
2024-07-28 firmware y hardware update
2024-07-28 fimware update
2024-07-29 modelos 3D base de pruebas
2024-07-29 uso ADC 2
2024-07-29 compilado
2024-08-11 Enable Gate signal
2024-08-30 test_socket
2024-09-03 update 030924
2024-09-04 debugs
2024-09-14 update 140924
2024-09-14 manuscrito semana 1
2024-09-15 gráficos
2024-09-23 update 220924
2024-11-10 image update
2025-01-14 primera entrega 130125
2025-08-05 publicación publica
2025-08-05 reorganización
2025-08-05 hal update
